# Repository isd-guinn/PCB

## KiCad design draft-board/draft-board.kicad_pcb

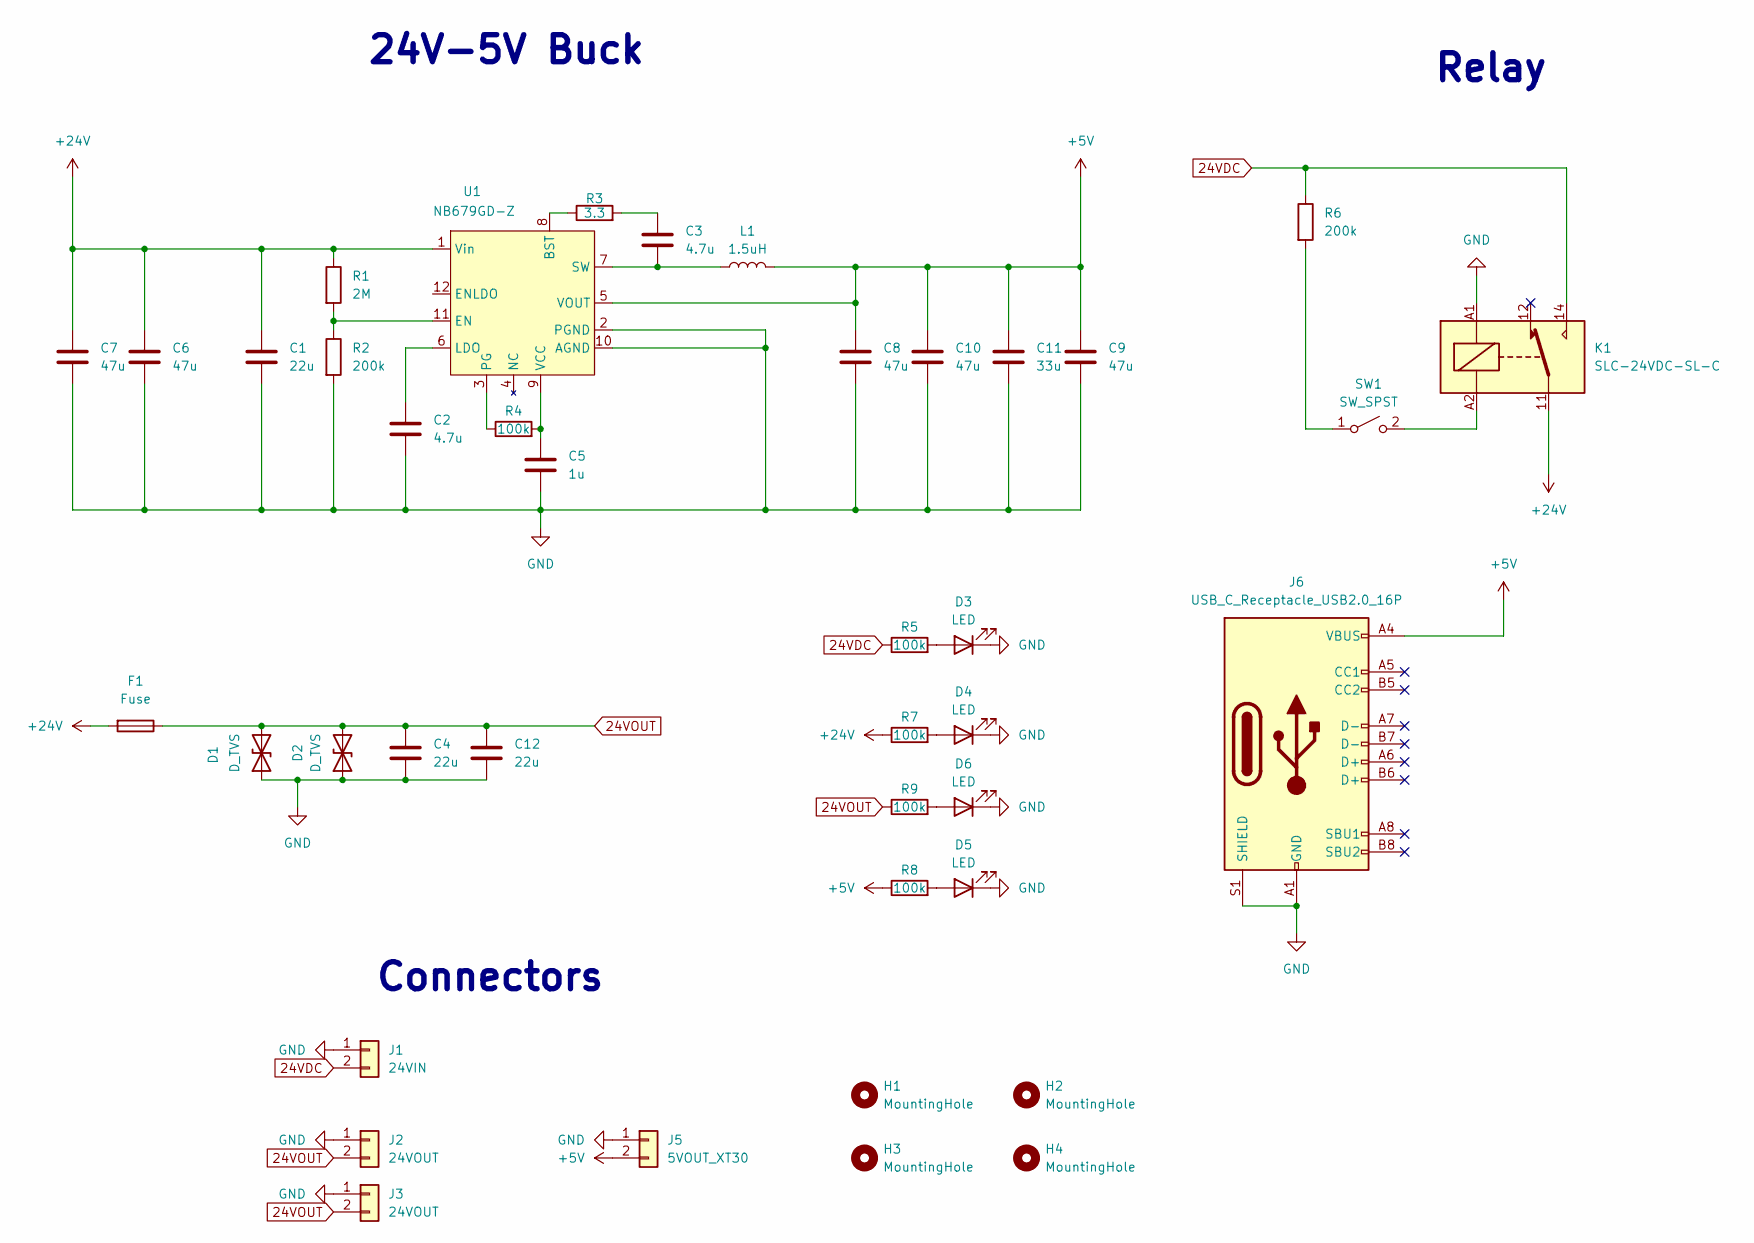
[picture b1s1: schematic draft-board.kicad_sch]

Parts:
C1: 22u; CP_Elec_6.3x7.7
C2, C3: 4.7u; C_0603_1608Metric
C4, C12: 22u; C_1206_3216Metric
C5: 1u; C_0603_1608Metric
C6, C7, C8, C9, C10: 47u; CP_Elec_6.3x7.7
C11: 33u; CP_Elec_6.3x7.7
D1, D2: D_TVS; D_SMA
D3, D4, D5, D6: LED; LED_0603_1608Metric
F1: Fuse; Fuseholder_Cylinder-5x20mm_Stelvio-Kontek_PTF78_Horizontal_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
H1, H2, H3, H4: MountingHole; MountingHole_3.2mm_M3_DIN965_Pad
J1: 24VIN; AMASS_XT60-F_1x02_P7.20mm_Vertical
J2, J3: 24VOUT; AMASS_XT30U-F_1x02_P5.0mm_Vertical
J5: 5VOUT_XT30; AMASS_XT30U-F_1x02_P5.0mm_Vertical
J6: USB_C_Receptacle_USB2.0_16P; USB_C_Receptacle_GCT_USB4105-xx-A_16P_TopMnt_Horizontal
K1: SLC-24VDC-SL-C; Relay_SPDT_RAYEX-L90S
L1: 1.5uH; L_Chilisin_BMRx00060630
R1: 2M; R_0603_1608Metric
R2, R6: 200k; R_0603_1608Metric
R3: 3.3; R_0603_1608Metric
R4, R5, R7, R8, R9: 100k; R_0603_1608Metric
SW1: SW_SPST; SW_DIP_SPSTx01_Slide_9.78x4.72mm_W7.62mm_P2.54mm
U1: NB679GD-Z; VREG_TPS51386RJNR

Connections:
24VDC: J1.2, K1.14, R5.1, R6.1
24VOUT: C4.1, C12.1, D1.2 (A2), D2.2 (A2), F1.1, J2.2, J3.2, R9.1
+5V: C8.1, C9.1, C10.1, C11.1, J5.2, J6.A4 (VBUS), J6.A9 (VBUS), J6.B4 (VBUS), J6.B9 (VBUS), L1.2, R8.1, U1.5 (VOUT)
+24V: C1.1, C6.1, C7.1, F1.2, K1.11, R1.1, R7.1, U1.1 (Vin)
GND: C1.2, C2.2, C4.2, C5.2, C6.2, C7.2, C8.2, C9.2, C10.2, C11.2, C12.2, D1.1 (A1), D2.1 (A1), D3.1 (K), D4.1 (K), D5.1 (K), D6.1 (K), J1.1, J2.1, J3.1, J5.1, J6.A1 (GND), J6.A12 (GND), J6.B1 (GND), J6.B12 (GND), J6.S1 (SHIELD), K1.A1, R2.2, U1.2 (PGND), U1.10 (AGND)
unnamed: C3.1, R3.2
unnamed: D3.2 (A), R5.2
unnamed: D4.2 (A), R7.2
unnamed: D5.2 (A), R8.2
unnamed: D6.2 (A), R9.2
unnamed: R6.2, SW1.1 (A)
unnamed: K1.A2, SW1.2 (B)
unnamed: R3.1, U1.8 (BST)
unnamed: R1.2, R2.1, U1.11 (EN)
unnamed: C2.1, U1.6 (LDO)
unnamed: R4.1, U1.3 (PG)
unnamed: C3.2, L1.1, U1.7 (SW)
unnamed: C5.1, R4.2, U1.9 (VCC)

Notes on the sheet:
24V-5V Buck
Connectors
Relay

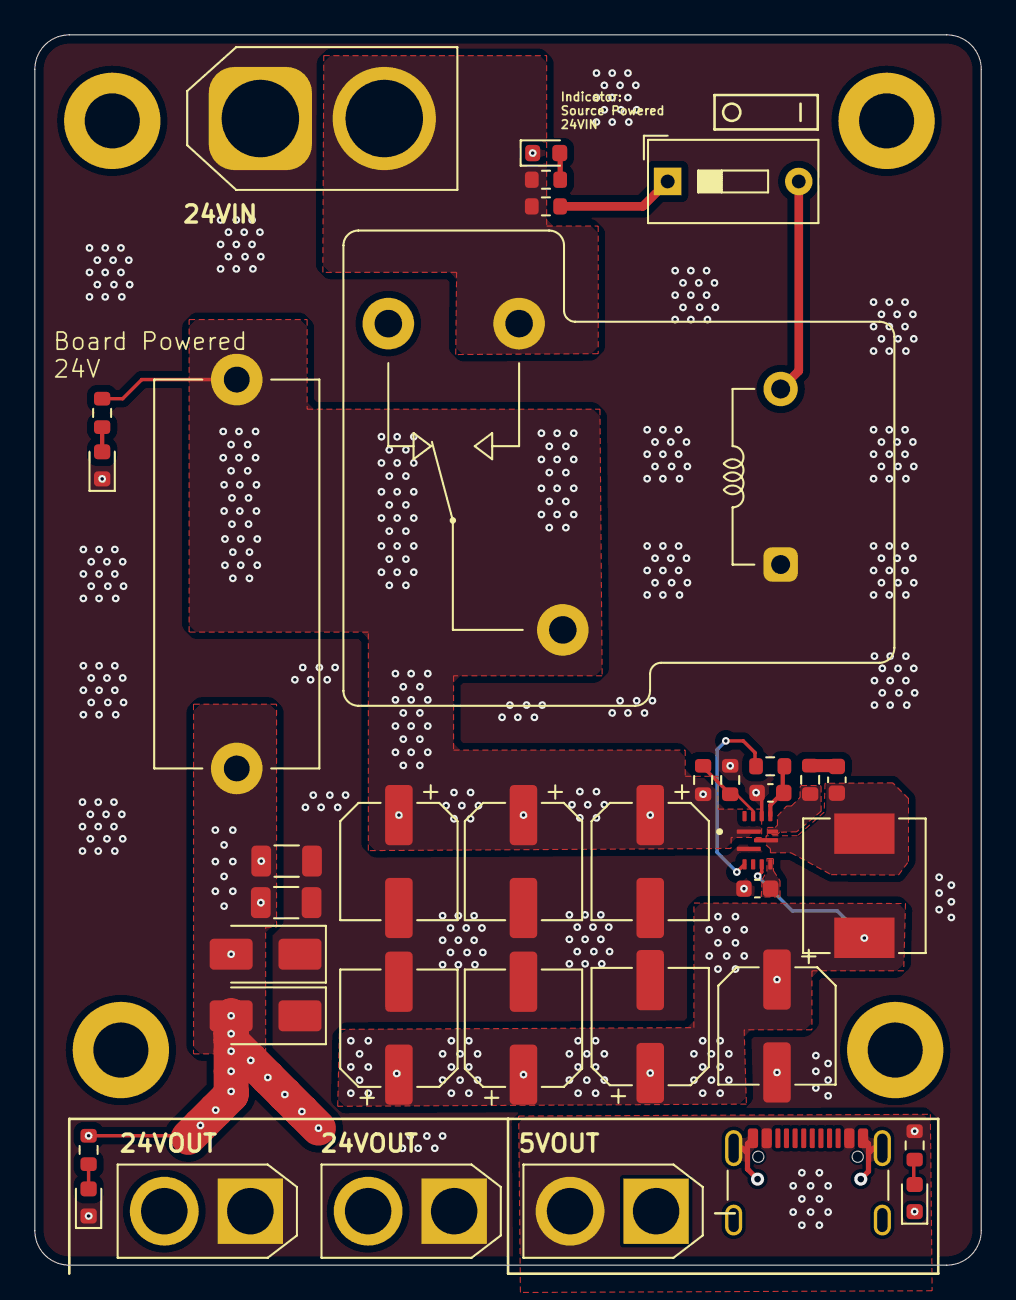
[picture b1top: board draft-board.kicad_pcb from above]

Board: 4 copper layers, 55.0 x 71.5 mm, 41 parts (0 on the bottom side), 18 nets.

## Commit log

2024-10-02 Buck and LDO
2024-10-03 start layout
2024-10-04 Finished layout
2024-10-04 polished layout
2024-10-04 Add back all files
2024-10-04 Polished 2nd time
2024-10-07 Production
2024-10-07 Production 2
